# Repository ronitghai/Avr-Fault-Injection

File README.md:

# Fault Injection on AES: Cryptographic Hardware Attack

### Overview
This project focused on exploiting vulnerabilities in AES encryption by inducing faults into embedded firmware running on an **ATMega328P** microcontroller and analyzing resulting data to recover the cipher key.

### Tech Stack
- **Firmware**: C/C++ on Arduino IDE
- **Microcontroller**: ATMega328P
- **Hardware Tools**: RP2040 (for fault injection), Zynq-7000 FPGA (initial testing)
- **Analysis**: Python (differential analysis)

### Key Features
- Implemented custom AES encryption in C on the victim MCU.
- Designed fault injection mechanism to corrupt encryption rounds.
- Collected and analyzed 1500 ciphertexts to extract partial cipher key.
- Used Python for statistical correlation and trace analysis.

### Development Summary
- Wrote both victim and attacker firmware in C.
- Designed fault injection testbed using GPIO-triggered timing delays.
- Switched to RP2040 for more precise glitching after testing with Zynq FPGA.
- Performed statistical analysis to reverse-engineer AES keys using Python scripts.

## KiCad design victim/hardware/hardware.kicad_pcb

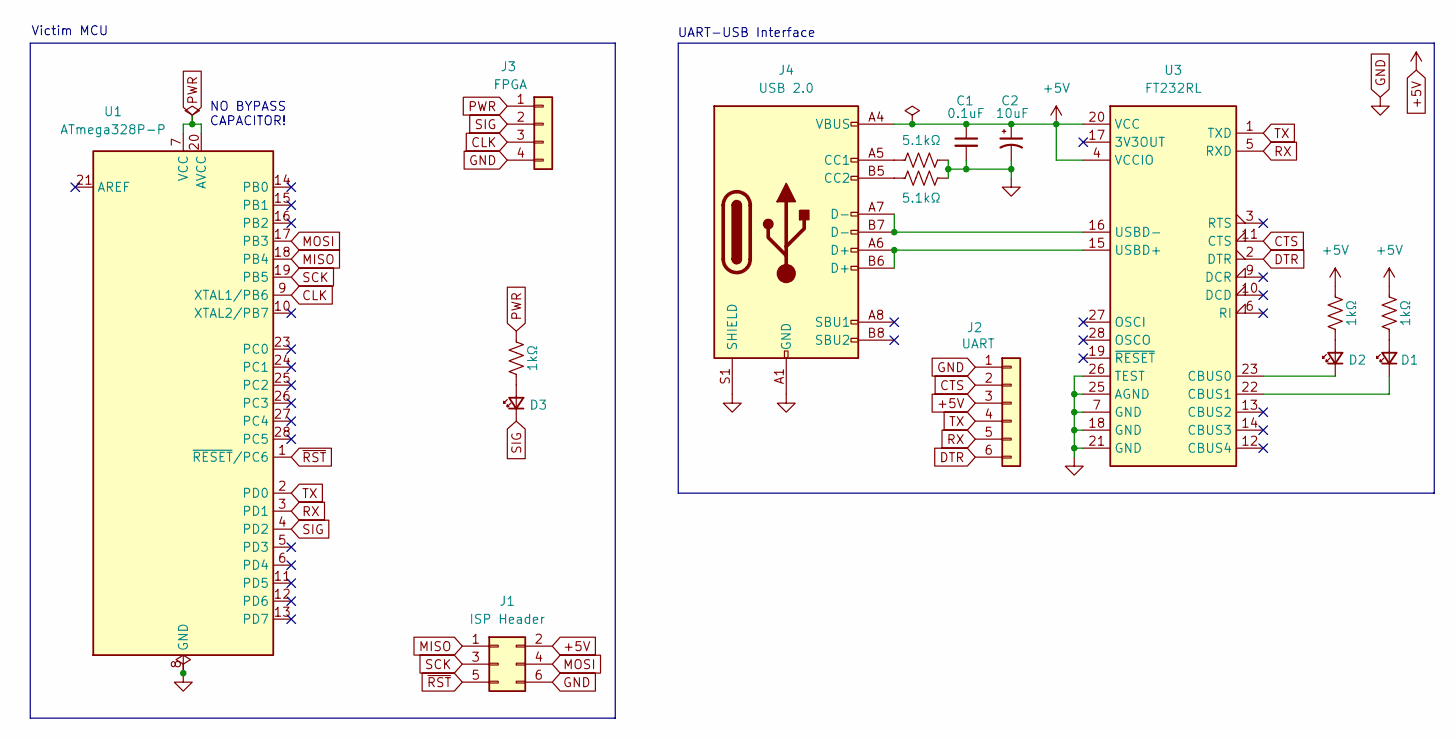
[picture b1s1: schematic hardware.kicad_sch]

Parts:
C1: 0.1uF; C_0805_2012Metric
C2: 10uF; C_0805_2012Metric
D1, D2, D3: LED_Small; LED_0805_2012Metric
J1: ISP Header; PinHeader_2x03_P2.54mm_Vertical
J2: UART; PinHeader_1x06_P2.54mm_Vertical
J3: FPGA; PinHeader_1x04_P2.54mm_Vertical
J4: USB 2.0; USB_C_Receptacle_G-Switch_GT-USB-7010ASV
R1, R2: 5.1kΩ; R_0805_2012Metric
R3, R4, R5: 1kΩ; R_0805_2012Metric
U1: ATmega328P-P; DIP-28_W7.62mm
U3: FT232RL; SSOP-28_5.3x10.2mm_P0.65mm

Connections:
+5V: C1.1, C2.1, J1.2, J2.3, J4.A4 (VBUS), J4.A9 (VBUS), J4.B4 (VBUS), J4.B9 (VBUS), R3.2, R4.2, U3.4 (VCCIO), U3.20 (VCC)
CLK: J3.3, U1.9 (XTAL1/PB6)
CTS: J2.2, U3.11 (CTS)
DTR: J2.6, U3.2 (DTR)
GND: C1.2, C2.2, J1.6, J2.1, J3.4, J4.A1 (GND), J4.A12 (GND), J4.B1 (GND), J4.B12 (GND), J4.S1 (SHIELD), R1.2, R2.2, U1.8 (GND), U1.22 (GND), U3.7 (GND), U3.18 (GND), U3.21 (GND), U3.25 (AGND), U3.26 (TEST)
MISO: J1.1, U1.18 (PB4)
MOSI: J1.4, U1.17 (PB3)
unnamed: D1.2 (A), R4.1
unnamed: D1.1 (K), U3.22 (CBUS1)
unnamed: D2.2 (A), R3.1
unnamed: D2.1 (K), U3.23 (CBUS0)
unnamed: D3.2 (A), R5.1
unnamed: J4.A5 (CC1), R1.1
unnamed: J4.B5 (CC2), R2.1
unnamed: J4.A6 (D+), J4.B6 (D+), U3.15 (USBD+)
unnamed: J4.A7 (D-), J4.B7 (D-), U3.16 (USBD-)
PWR: J3.1, R5.2, U1.7 (VCC), U1.20 (AVCC)
RX: J2.5, U1.3 (PD1), U3.5 (RXD)
SCK: J1.3, U1.19 (PB5)
SIG: D3.1 (K), J3.2, U1.4 (PD2)
TX: J2.4, U1.2 (PD0), U3.1 (TXD)
~RST: J1.5, U1.1 (~RESET/PC6)

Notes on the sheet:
NO BYPASS CAPACITOR!
UART-USB Interface
Victim MCU

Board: 2 copper layers, 16 parts (2 on the bottom side), 22 nets, no tracks yet.

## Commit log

2025-06-19 README.md
